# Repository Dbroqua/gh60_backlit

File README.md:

# Projet déplacé vers [framagit](https://framagit.org/mechkeyboards/gh60_backlit)

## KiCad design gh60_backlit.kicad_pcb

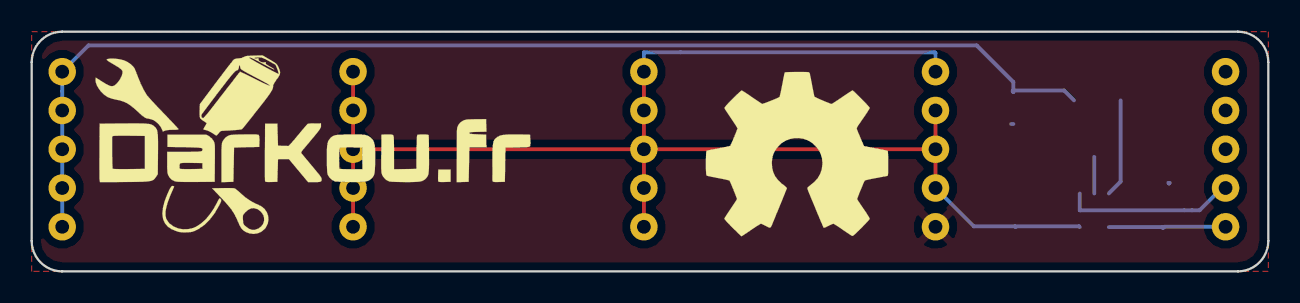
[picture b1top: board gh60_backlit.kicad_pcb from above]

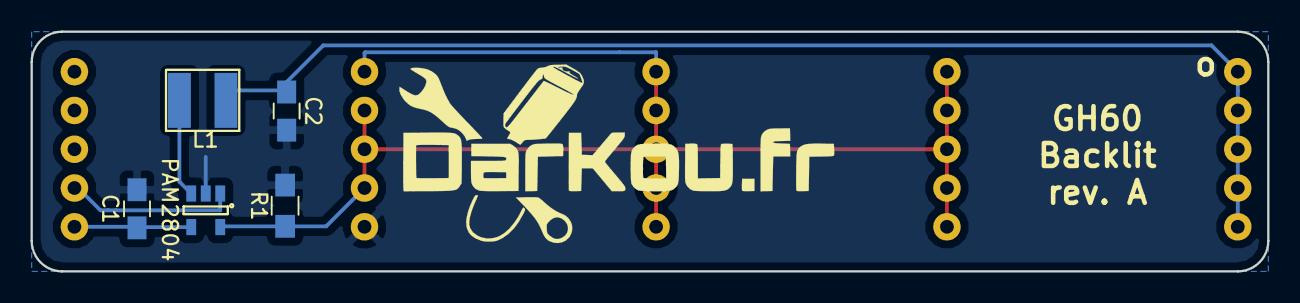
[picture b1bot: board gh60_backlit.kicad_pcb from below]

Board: 2 copper layers, 81.0 x 15.7 mm, 10 parts (5 on the bottom side), 6 nets.

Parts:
5_PIN_HEADER0, 5_PIN_HEADER1, 5_PIN_HEADER2, 5_PIN_HEADER3, 5_PIN_HEADER4: 5_PIN_HEADER; 5PIN_HEADER
C1, C2: 10uF; C_0805_HandSoldering
L1: 4.7uH; Inductor_Bourn_4mmx4mm
R1: R; R_0805_HandSoldering
U1: PAM2804; SOT-23-5

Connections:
GND: 5_PIN_HEADER3.1, C1.2, C2.2, R1.2, U1.2
GPIO2: 5_PIN_HEADER4.2, U1.1
LCOL1: 5_PIN_HEADER1.1, 5_PIN_HEADER1.2, 5_PIN_HEADER1.3, 5_PIN_HEADER1.4, 5_PIN_HEADER1.5, 5_PIN_HEADER2.1, 5_PIN_HEADER2.2, 5_PIN_HEADER2.3, 5_PIN_HEADER2.4, 5_PIN_HEADER2.5, 5_PIN_HEADER3.2, 5_PIN_HEADER3.3, 5_PIN_HEADER3.4, 5_PIN_HEADER3.5, R1.1, U1.5
LROW1: 5_PIN_HEADER0.1, 5_PIN_HEADER0.2, 5_PIN_HEADER0.3, 5_PIN_HEADER0.4, 5_PIN_HEADER0.5, C2.1, L1.2
unnamed: L1.1, U1.3
VCC: 5_PIN_HEADER4.1, C1.1, U1.4

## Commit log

2017-10-25 Initial commit with first design
2017-10-25 Increased GND areas
2017-10-26 Fixed bug on wiring
    Rotated for pin header with GND and VCC.
2017-10-26 Updated scheme
    Added resistor value and datasheet/manf# to all components
